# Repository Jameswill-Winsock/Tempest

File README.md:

# Tempest : Open Hardware EM Side-Channel Analysis Platform

## Important:
if you are here looking for review, firmware, gerber and pcb have been updated. Step models have been added.
Firmware is a fork of the SIPEED RV Debugger Plus, ported from the BL507 to the RP2040.
All pcb files and gerbers have been uploaded for the carrier board for the primer. All pcbs are done.

latest readme for progress on the attack target available [here](rtl/shrike_accel_v1/readme.md).

# Status
Early build. Built for Stardance @ Hack Club.

# Current progress

## Done:
- Shrike-Lite ML-KEM accelerator is functionally complete (currently fighting Renesas place-and-route to get the final bitstream out).
- Finished designing the Tang Primer 20K carrier board.

- Finished designing the H Field Probe

## In progress:
Demo video. Give me a while. Renesas Go Configure is quite the software, and the place-and-route tool keeps blowing up violently in my face.

# Description

Tempest is an open hardware electromagnetic side-channel analysis platform built around a collection of custom-designed PCBs, analog front-end hardware, FPGA development boards, and open-source software for evaluating cryptographic implementations.

Or, in simpler English:
Every chip leaks tiny electromagnetic signals while it's running. Those signals aren't supposed to contain useful information... but sometimes they do. Tempest tries to measure those leaks and figure out whether they reveal anything about the cryptographic algorithm running inside.
The project is built around Shrike-Lite, my ML-KEM (Kyber) hardware accelerator running on a hilariously tiny Renesas SLG47910 FPGA. Shrike answers one question: "Can modern post-quantum cryptography fit on ridiculously small hardware?"
Tempest answers the obvious follow-up: "Cool. *Now how badly does it leak?* 
". 
Rather than buying a commercial side-channel lab, the goal is to design as much of the measurement hardware as possible from scratch so anyone can build the same setup themselves.

## Why EM instead of power analysis?

Power analysis is the classic approach.
The problem is... it usually means taking a knife to your PCB. You know, cut traces, insert shunt resistors, resolder stuff. That's perfectly fine on a $2 dev board. I ain't sure as hell doing allat to a motherboard I actually want to keep using afterwards.
EM analysis measures the exact same switching currents, except instead of touching the power rail, you simply hold a small magnetic loop probe near the chip and measure the field it radiates. It's completely non-invasive, portable, and lets me move between different targets without modifying the hardware.

# Project Architecture

Tempest is really two projects that work together.
```
Shrike
(Resource-constrained ML-KEM accelerator)

            ↓

Produces real electromagnetic leakage

            ↓

Tempest
(Open hardware instrumentation platform)

            ↓

Measures leakage

            ↓

Correlation analysis

            ↓

Can we recover useful information?
```

**The long-term hardware stack looks like this:**
```
Target FPGA / TPM
        │
        ▼
Shielded EM Probe
        │
        ▼
Active Probe + LNA
        │
        ▼
Filter / Analog Front-End
        │
        ▼
Capture Hardware
        │
        ▼
Python Analysis Pipeline
```
# Hardware Designed For This Project

| Hardware | Status |
|---|---|
|Shrike-Lite ML-KEM Accelerator | Complete (bitstream generation pending) |
|Tang Primer 20K Carrier Board | Complete |
|Shielded PCB EM Probe | Complete |
|Probe Calibration Board | Complete |

# Roadmap
- Finish Shrike-Lite bring-up.
- Build and validate a passive EM probe.
- Build a calibration board to characterize probe performance.
- Validate the analog front-end on a deliberately leaky AES implementation before touching Kyber.
- Build the trigger/synchronization pipeline.
- Perform correlation EM analysis against Shrike-Lite.
- Scale to the Tang Primer 20K as a larger TPM stand-in.
- Eventually move to a real motherboard TPM once the entire workflow is validated.

# Original Hardware Contributions
Unlike the initial revision of this project, Tempest now focuses on designing the measurement hardware itself rather than simply integrating commercial equipment. Current hardware work includes:
- Tang Primer 20K carrier board
- Shielded PCB EM probe
- Probe calibration fixture

# Bill of Materials

| Item | Est. Price (USD) | Source | Why |
|---|---|---|---|
|Tang Nano 20k | $40 | [Robu](https://robu.in/product/sipeed-tang-nano-20k-fpga-devlopment-board/) | Main FPGA for ADC, SDR, trigger generation, timing/synchronization, counters, buffering/FIFOs, and control logic |
|Tang Primer 20K Carrier PCB | ~$20 | Self-designed | Carrier for the Primer module (I already own the core board) |
|Passive Probe PCB | ~$15 | Self-designed | Shielded PCB H-field probe, source IEC 61967-6 |
|Probe Calibration PCB | ~$15 | Self-designed | Repeatable EM reference source, source IEC 61967-6 Appendix A |
|SPF5189Z RF Low Noise Amplifier | $15 | [REE52](https://rees52.com/products/spf5189z-rf-low-noise-amplifier-50-4000mhz-rf-lna-spf5189-0-6db-nf-phemt-mmic-rf-low-noise-amplifier-rs5090) | To boost passive probe signal |
|SMA Connectors, RG178, Adapters, Attenuators |	$30–60 | [Pasternack](https://www.pasternack.com/), [Amphenol](https://www.amphenolrf.com/en-us/), [Mini-Circuits](https://www.minicircuits.com/) | RF interconnects |
|PCB fabrication & assembly | ~$50 | JLCPCB | Manufacturing the custom boards

**Grand total**: approx 215$ (down from last times 400$ yipee)
The oscilloscope, precision positioning stage, and laboratory power supply have been removed from the grant request. The initial revision of Tempest is designed to be developed using low-cost hardware and custom-designed PCBs, with higher-end laboratory equipment treated as optional future upgrades rather than project requirements.
**BOM Revision 2**: The Tang Mega 138K, Thorlabs positioning equipment, and benchtop power supply have been removed due to cost. They have been replaced with lower-cost alternatives where necessary. A second, lower-cost FPGA is still required for <u>SDR, ADC, high-speed deterministic logic, trigger generation, timing/synchronization, buffering, and real-time control,</u> which cannot be reliably handled by the host computer or RTL-SDR alone.
**BOM Revision 3**: More stuff removed, I have discovered that I can offload a lot more stuff to the FPGA like ADC and SDR onto it via a research paper and other stuff as well. Cost has been bought down. Final cost is around approx 230$.

# Repository Layout
- rtl: Shrike-Lite accelerator, Future hardware targets

- hardware: KiCad projects, Carrier board, Probe board

- analysis: Capture software, CPA/CEMA pipeline

- docs: Research notes, Measurements, Design reviews

# Why this matters

Most public EM side-channel work either targets toy AES implementations or uses lab-grade near-field scanning rigs that cost tens of thousands of dollars. There's a real gap in documented, reproducible, low-cost EM side-channel analysis against post-quantum crypto specifically; ML-KEM side-channel resistance is an active research area (and a pretty hot one too - there's a hell lot of researchers taking a crack at it) and having a from-scratch hardware+software stack to poke at it is worth more to me than a paper result I can't independently reproduce.

If it works, you'll be able to:
- build the hardware,
- reproduce the measurements,
- attack real cryptographic implementations,
- and improve your own hardware designs by seeing exactly where they leak.

Besides...
The math behind modern cryptography is ridiculously strong. Turns out the easiest way to break it is often just listening to the chip while it does the math. It's cool, isn't it? The math can't be cracked, but we sure as hell can crack the data anyways because of bad engineering decisions. :)

# License
GNU GPLv3

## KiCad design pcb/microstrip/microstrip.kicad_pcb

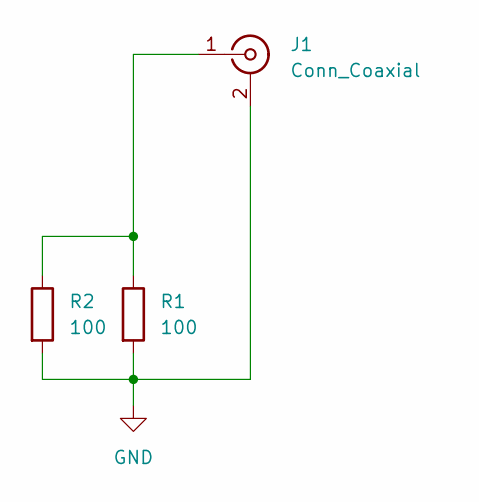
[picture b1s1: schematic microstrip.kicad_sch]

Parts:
J1: Conn_Coaxial; SMA_Amphenol_132289_EdgeMount
R1, R2: 100; R_0603_1608Metric

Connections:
GND: J1.2 (Ext), R1.2, R2.2
unnamed: J1.1 (In), R1.1, R2.1

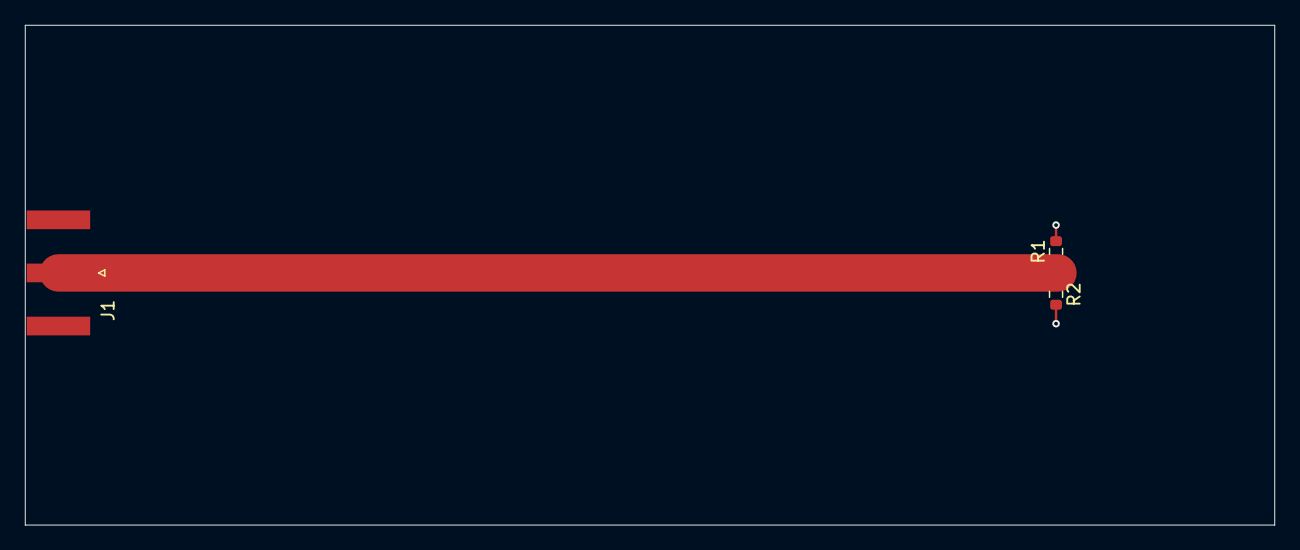
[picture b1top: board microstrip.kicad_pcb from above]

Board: 2 copper layers, 100.0 x 40.0 mm, 3 parts (0 on the bottom side), 2 nets.

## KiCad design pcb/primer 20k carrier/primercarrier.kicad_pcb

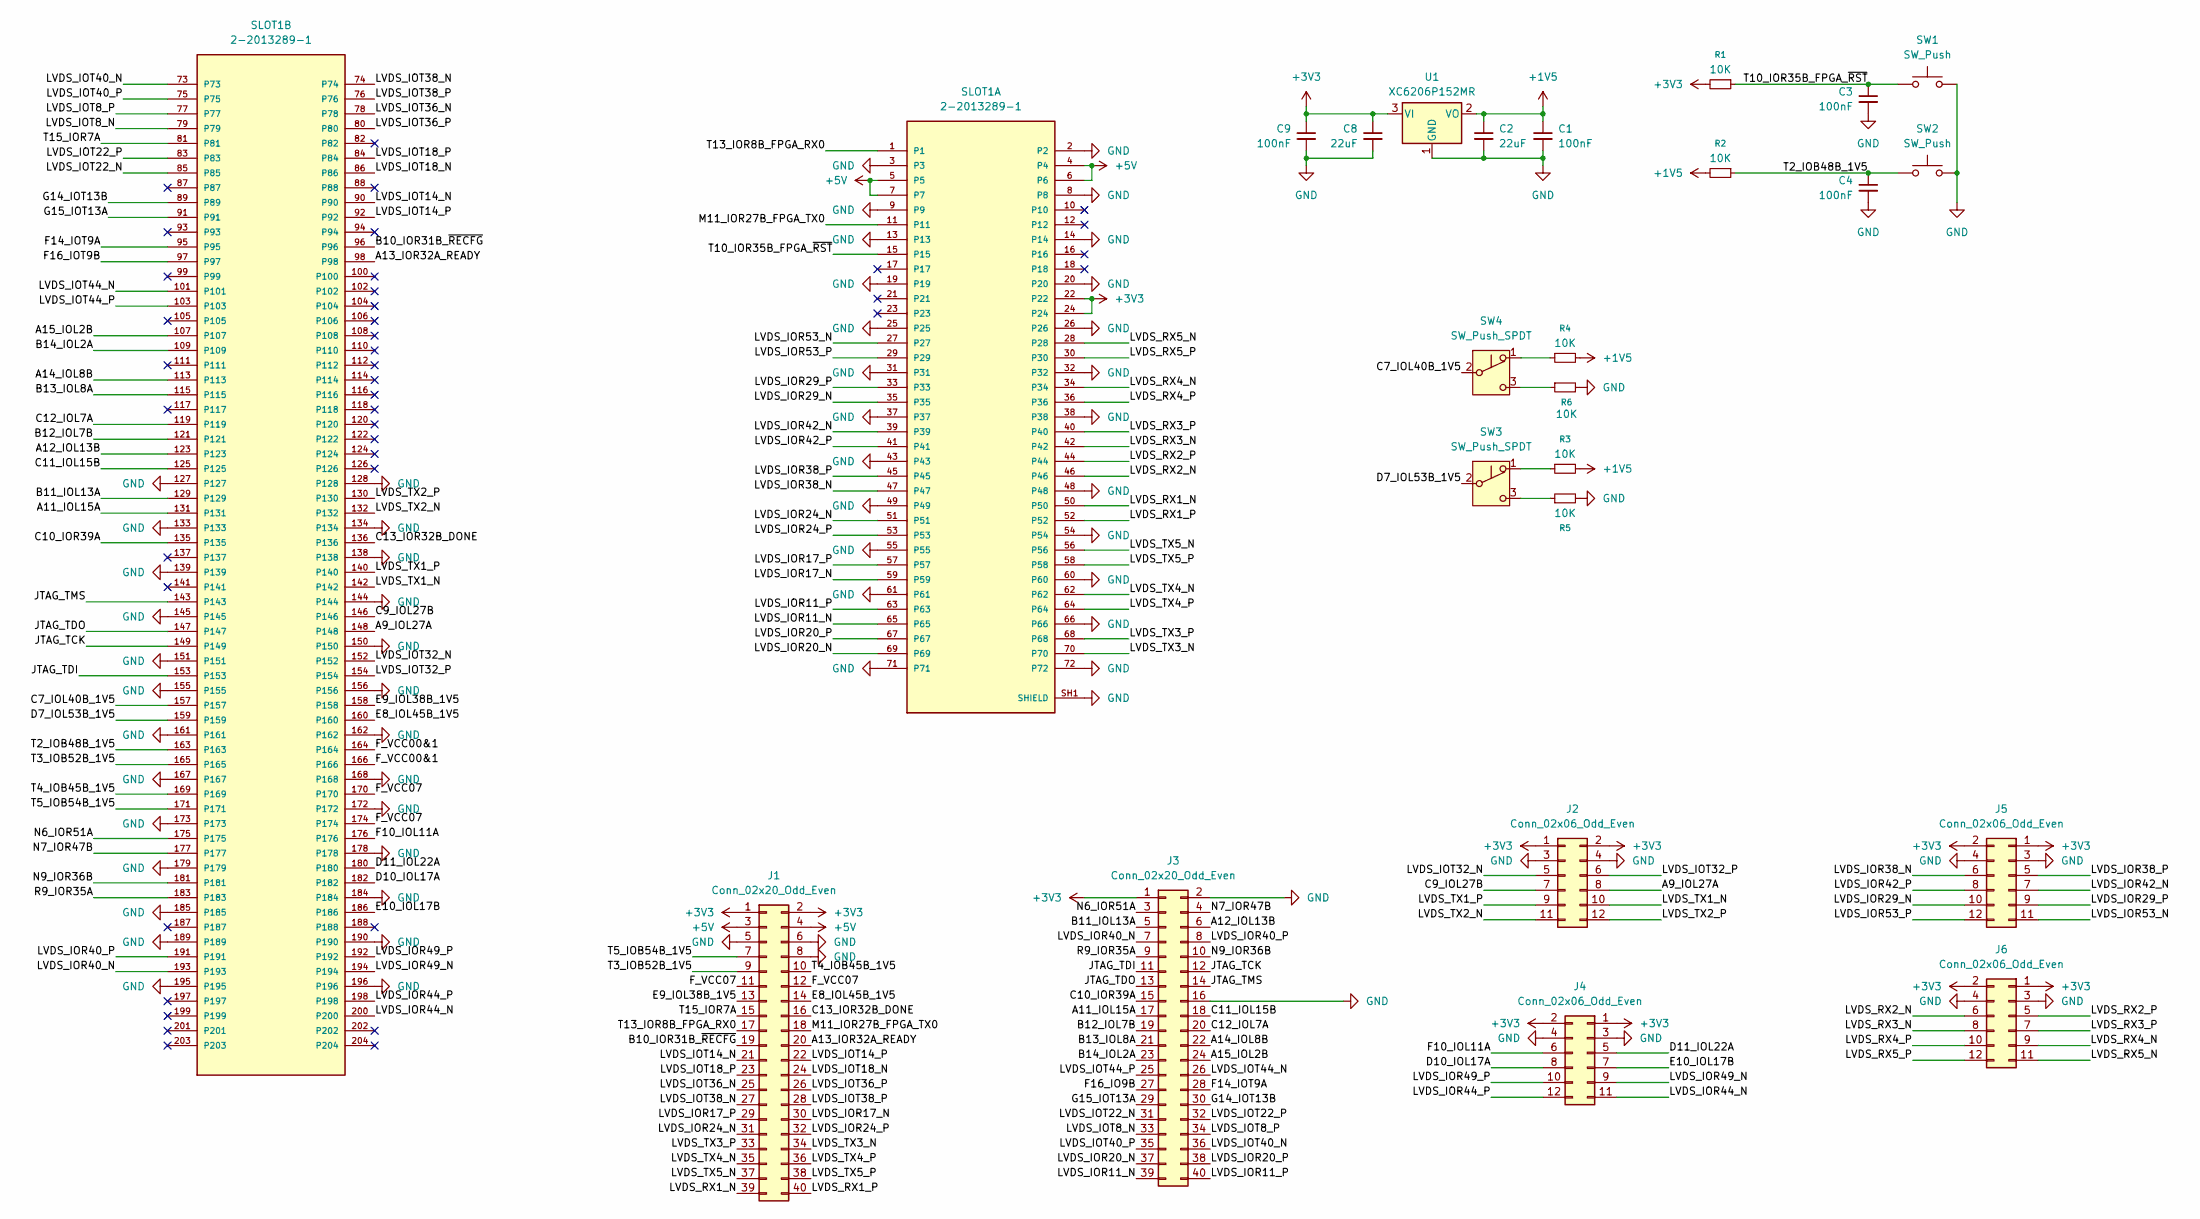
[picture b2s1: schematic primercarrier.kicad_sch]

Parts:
C1, C3, C4, C9: 100nF; C_0402_1005Metric
C2, C8: 22uF; C_0603_1608Metric
J1, J3: Conn_02x20_Odd_Even; PinHeader_2x20_P2.54mm_Vertical
J2, J4, J5, J6: Conn_02x06_Odd_Even; PinHeader_2x06_P2.54mm_Vertical
R1, R2, R3, R4, R5, R6: 10K; R_0402_1005Metric
SLOT1: 2-2013289-1; SODIMM-204; VOLTAGE_RATING_DC 1.5; PART_DESCRIPTION CONN SKT SODIMM 204POS SMD; DigiKey_Part_Number A116236CT-ND
SW1, SW2: SW_Push; SW_SPST_TL3342
SW3, SW4: SW_Push_SPDT; SW_Push_1P2T_Vertical_E-Switch_800UDP8P1A1M6
U1: XC6206P152MR; SOT-23-3

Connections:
+1V5: C1.1, C2.1, R2.2, R3.2, R4.2, U1.2 (VO)
+3V3: C8.1, C9.1, J1.1, J1.2, J2.1, J2.2, J3.1, J4.1, J4.2, J5.1, J5.2, J6.1, J6.2, R1.2, SLOT1.22, SLOT1.24, U1.3 (VI)
+5V: J1.3, J1.4, SLOT1.4, SLOT1.5, SLOT1.6, SLOT1.7
/A9_IOL27A: J2.8, SLOT1.148
/A11_IOL15A: J3.17, SLOT1.131
/A12_IOL13B: J3.6, SLOT1.123
/A13_IOR32A_READY: J1.20, SLOT1.98
/A14_IOL8B: J3.22, SLOT1.113
/A15_IOL2B: J3.24, SLOT1.107
/B10_IOR31B_~RECFG: J1.19, SLOT1.96
/B11_IOL13A: J3.5, SLOT1.129
/B12_IOL7B: J3.19, SLOT1.121
/B13_IOL8A: J3.21, SLOT1.115
/B14_IOL2A: J3.23, SLOT1.109
/C7_IOL40B_1V5: SLOT1.157, SW4.2 (B)
/C9_IOL27B: J2.7, SLOT1.146
/C10_IOR39A: J3.15, SLOT1.135
/C11_IOL15B: J3.18, SLOT1.125
/C12_IOL7A: J3.20, SLOT1.119
/C13_IOR32B_DONE: J1.16, SLOT1.136
/D7_IOL53B_1V5: SLOT1.159, SW3.2 (B)
/D10_IOL17A: J4.8, SLOT1.182
/D11_IOL22A: J4.5, SLOT1.180
/E8_IOL45B_1V5: J1.14, SLOT1.160
/E9_IOL38B_1V5: J1.13, SLOT1.158
/E10_IOL17B: J4.7, SLOT1.186
/F10_IOL11A: J4.6, SLOT1.176
/F14_IOT9A: J3.28, SLOT1.95
/F16_IO9B: J3.27
/F16_IOT9B: SLOT1.97
/F_VCC00&1: SLOT1.164, SLOT1.166
/F_VCC07: J1.11, J1.12, SLOT1.170, SLOT1.174
/G14_IOT13B: J3.30, SLOT1.89
/G15_IOT13A: J3.29, SLOT1.91
/JTAG_TCK: J3.12, SLOT1.149
/JTAG_TDI: J3.11, SLOT1.153
/JTAG_TDO: J3.13, SLOT1.147
/JTAG_TMS: J3.14, SLOT1.143
/LVDS_IOR11_N: J3.39, SLOT1.65
/LVDS_IOR11_P: J3.40, SLOT1.63
/LVDS_IOR17_N: J1.30, SLOT1.59
/LVDS_IOR17_P: J1.29, SLOT1.57
/LVDS_IOR20_N: J3.37, SLOT1.69
/LVDS_IOR20_P: J3.38, SLOT1.67
/LVDS_IOR24_N: J1.31, SLOT1.51
/LVDS_IOR24_P: J1.32, SLOT1.53
/LVDS_IOR29_N: J5.10, SLOT1.35
/LVDS_IOR29_P: J5.9, SLOT1.33
/LVDS_IOR38_N: J5.6, SLOT1.47
/LVDS_IOR38_P: J5.5, SLOT1.45
/LVDS_IOR40_N: J3.7, SLOT1.193
/LVDS_IOR40_P: J3.8, SLOT1.191
/LVDS_IOR42_N: J5.7, SLOT1.39
/LVDS_IOR42_P: J5.8, SLOT1.41
/LVDS_IOR44_N: J4.11, SLOT1.200
/LVDS_IOR44_P: J4.12, SLOT1.198
/LVDS_IOR49_N: J4.9, SLOT1.194
/LVDS_IOR49_P: J4.10, SLOT1.192
/LVDS_IOR53_N: J5.11, SLOT1.27
/LVDS_IOR53_P: J5.12, SLOT1.29
/LVDS_IOT8_N: J3.33, SLOT1.79
/LVDS_IOT8_P: J3.34, SLOT1.77
/LVDS_IOT14_N: J1.21, SLOT1.90
/LVDS_IOT14_P: J1.22, SLOT1.92
/LVDS_IOT18_N: J1.24, SLOT1.86
/LVDS_IOT18_P: J1.23, SLOT1.84
/LVDS_IOT22_N: J3.31, SLOT1.85
/LVDS_IOT22_P: J3.32, SLOT1.83
/LVDS_IOT32_N: J2.5, SLOT1.152
/LVDS_IOT32_P: J2.6, SLOT1.154
/LVDS_IOT36_N: J1.25, SLOT1.78
/LVDS_IOT36_P: J1.26, SLOT1.80
/LVDS_IOT38_N: J1.27, SLOT1.74
/LVDS_IOT38_P: J1.28, SLOT1.76
/LVDS_IOT40_N: J3.36, SLOT1.73
/LVDS_IOT40_P: J3.35, SLOT1.75
/LVDS_IOT44_N: J3.26, SLOT1.101
/LVDS_IOT44_P: J3.25, SLOT1.103
/LVDS_RX1_N: J1.39, SLOT1.50
/LVDS_RX1_P: J1.40, SLOT1.52
/LVDS_RX2_N: J6.6, SLOT1.46
/LVDS_RX2_P: J6.5, SLOT1.44
/LVDS_RX3_N: J6.8, SLOT1.42
/LVDS_RX3_P: J6.7, SLOT1.40
/LVDS_RX4_N: J6.9, SLOT1.34
/LVDS_RX4_P: J6.10, SLOT1.36
/LVDS_RX5_N: J6.11, SLOT1.28
/LVDS_RX5_P: J6.12, SLOT1.30
/LVDS_TX1_N: J2.10, SLOT1.142
/LVDS_TX1_P: J2.9, SLOT1.140
/LVDS_TX2_N: J2.11, SLOT1.132
/LVDS_TX2_P: J2.12, SLOT1.130
/LVDS_TX3_N: J1.34, SLOT1.70
/LVDS_TX3_P: J1.33, SLOT1.68
/LVDS_TX4_N: J1.35, SLOT1.62
/LVDS_TX4_P: J1.36, SLOT1.64
/LVDS_TX5_N: J1.37, SLOT1.56
/LVDS_TX5_P: J1.38, SLOT1.58
/M11_IOR27B_FPGA_TX0: J1.18, SLOT1.11
/N6_IOR51A: J3.3, SLOT1.175
/N7_IOR47B: J3.4, SLOT1.177
/N9_IOR36B: J3.10, SLOT1.181
/R9_IOR35A: J3.9, SLOT1.183
/T2_IOB48B_1V5: C4.1, R2.1, SLOT1.163, SW2.1
/T3_IOB52B_1V5: J1.9, SLOT1.165
/T4_IOB45B_1V5: J1.10, SLOT1.169
/T5_IOB54B_1V5: J1.7, SLOT1.171
/T10_IOR35B_FPGA_~RST: C3.1, R1.1, SLOT1.15, SW1.1
/T13_IOR8B_FPGA_RX0: J1.17, SLOT1.1
/T15_IOR7A: J1.15, SLOT1.81
GND: C1.2, C2.2, C3.2, C4.2, C8.2, C9.2, J1.5, J1.6, J1.8, J2.3, J2.4, J3.2, J3.16, J4.3, J4.4, J5.3, J5.4, J6.3, J6.4, R5.2, R6.2, SLOT1.2, SLOT1.3, SLOT1.8, SLOT1.9, SLOT1.13, SLOT1.14, SLOT1.19, SLOT1.20, SLOT1.25, SLOT1.26, SLOT1.31, SLOT1.32, SLOT1.37, SLOT1.38, SLOT1.43, SLOT1.48, SLOT1.49, SLOT1.54, SLOT1.55, SLOT1.60, SLOT1.61, SLOT1.66, SLOT1.71, SLOT1.72, SLOT1.127, SLOT1.128, SLOT1.133, SLOT1.134, SLOT1.138, SLOT1.139, SLOT1.144, SLOT1.145, SLOT1.150, SLOT1.151, SLOT1.155, SLOT1.156, SLOT1.161, SLOT1.162, SLOT1.167, SLOT1.168, SLOT1.172, SLOT1.173, SLOT1.178, SLOT1.179, SLOT1.184, SLOT1.185, SLOT1.189, SLOT1.190, SLOT1.195, SLOT1.196, SLOT1.SH1 (SHIELD), SLOT1.SH2 (SHIELD), SW1.2, SW2.2, U1.1 (GND)
unnamed: R3.1, SW3.1 (A)
unnamed: R5.1, SW3.3 (C)
unnamed: R4.1, SW4.1 (A)
unnamed: R6.1, SW4.3 (C)

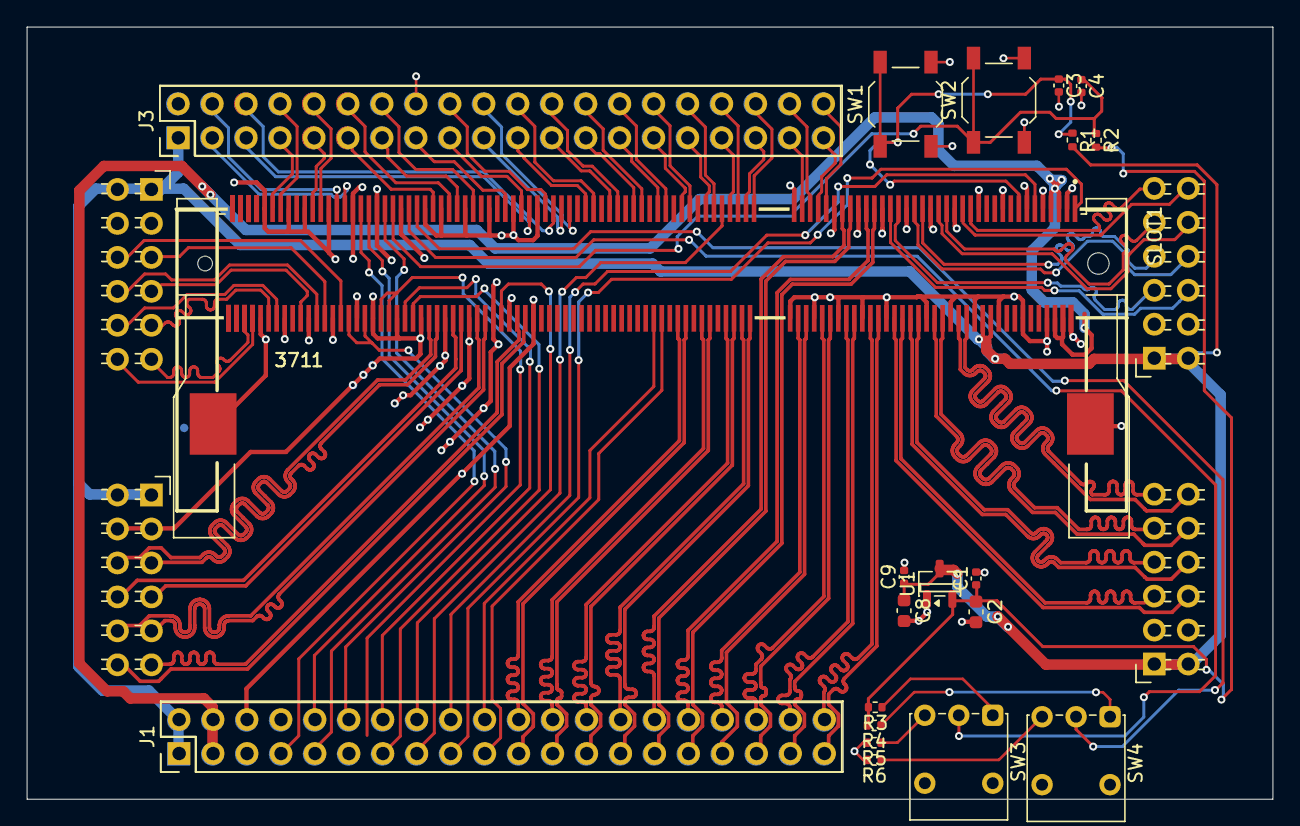
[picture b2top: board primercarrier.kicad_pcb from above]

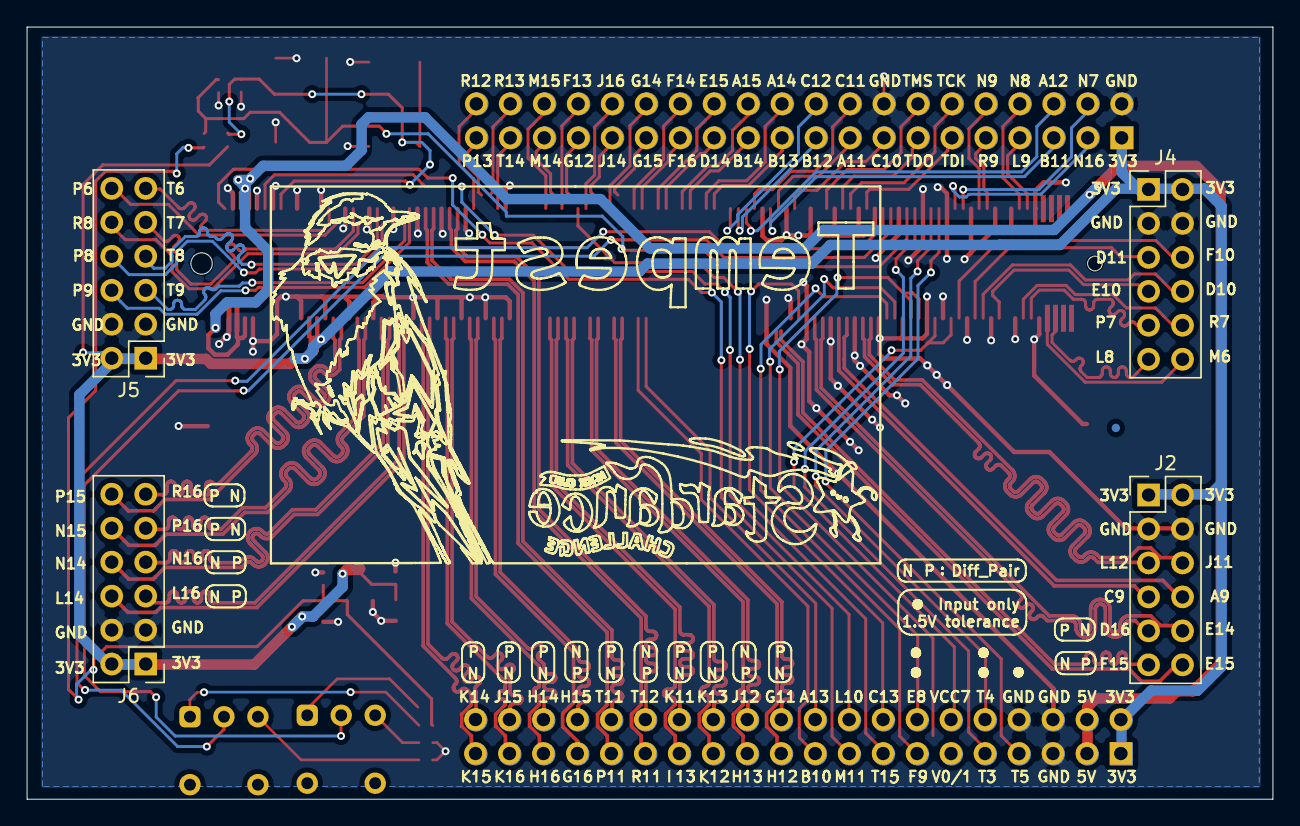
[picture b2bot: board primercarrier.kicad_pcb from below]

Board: 2 copper layers, 93.2 x 57.7 mm, 24 parts (4 on the bottom side), 113 nets.

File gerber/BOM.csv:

"Reference","Qty","Value","DNP","Exclude from BOM","Exclude from Board","Exclude from Simulation","Exclude from Position Files","Footprint","Datasheet"
"C1,C3,C4,C9","4","100nF","","","","","${EXCLUDE_FROM_POS_FILES}","Capacitor_SMD:C_0402_1005Metric",""
"C2,C8","2","22uF","","","","","${EXCLUDE_FROM_POS_FILES}","Capacitor_SMD:C_0603_1608Metric",""
"J1,J3","2","Conn_02x20_Odd_Even","","","","","${EXCLUDE_FROM_POS_FILES}","Connector_PinHeader_2.54mm:PinHeader_2x20_P2.54mm_Vertical",""
"J2,J4,J5,J6","4","Conn_02x06_Odd_Even","","","","","${EXCLUDE_FROM_POS_FILES}","Connector_PinHeader_2.54mm:PinHeader_2x06_P2.54mm_Vertical",""
"R1,R2,R3,R4,R5,R6","6","10K","","","","","${EXCLUDE_FROM_POS_FILES}","Resistor_SMD:R_0402_1005Metric",""
"SLOT1","1","2-2013289-1","","","","","${EXCLUDE_FROM_POS_FILES}","sodimm:SODIMM-204",""
"SW1,SW2","2","SW_Push","","","","","${EXCLUDE_FROM_POS_FILES}","Button_Switch_SMD:SW_SPST_TL3342",""
"SW3,SW4","2","SW_Push_SPDT","","","","","${EXCLUDE_FROM_POS_FILES}","Button_Switch_THT:SW_Push_1P2T_Vertical_E-Switch_800UDP8P1A1M6",""
"U1","1","XC6206P152MR","","","","","${EXCLUDE_FROM_POS_FILES}","Package_TO_SOT_SMD:SOT-23-3","https://www.torexsemi.com/file/xc6206/XC6206.pdf"
